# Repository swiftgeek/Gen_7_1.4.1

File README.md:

Known issues:

* PA6 missing trace to MCU and a short between PA6/PA7. Upstream `.pcb` file
doesn't match gerbers and PDFs/PNGs
* Board outline doesn't work well with OBV

TODO:

* Try importing gerber traces/layout into `pcb`/`pcbnew`, otherwise
set gerber render and background and try laying traces over it exactly.
* Generate PDFs and gerbers once fixed

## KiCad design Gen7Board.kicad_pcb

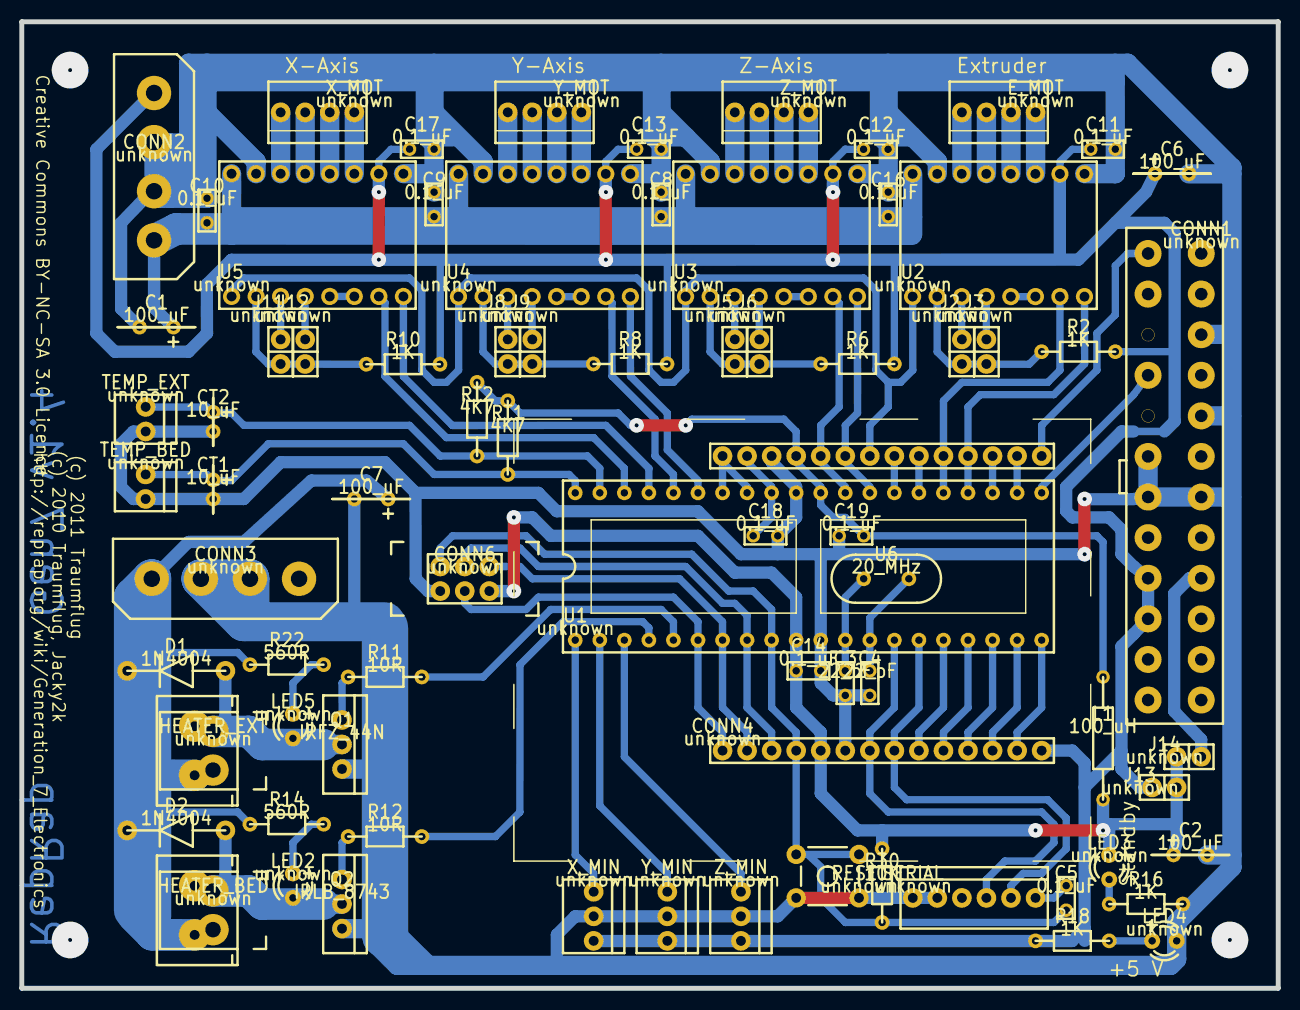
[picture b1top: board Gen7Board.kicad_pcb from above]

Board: 2 copper layers, 130.0 x 100.0 mm, 76 parts (0 on the bottom side), 84 nets.

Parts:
C1: 100_uF; RCY3mm5_dup15
C2: 100_uF; RCY3mm5_dup26
C3: 22_pF; ACY100_dup1
C4: 22_pF; ACY100_dup13
C5: 0.1_uF; ACY100_dup7
C6: 100_uF; RCY3mm5
C7: 100_uF; RCY3mm5_dup42
C8: 0.1_uF; ACY100_dup36
C9: 0.1_uF; ACY100_dup37
C10: 0.1_uF; ACY100_dup38
C11: 0.1_uF; ACY100_dup39
C12: 0.1_uF; ACY100
C13: 0.1_uF; ACY100_dup0
C14: 0.1_uF; ACY100_dup2
C16: 0.1_uF; ACY100_dup14
C17: 0.1_uF; ACY100_dup33
C18: 0.1_uF; ACY100_dup34
C19: 0.1_uF; ACY100_dup35
CONN1: unknown; ATX20+4-1
CONN2: unknown; MOLEX_4_PIN
CONN3: unknown; MOLEX_4_PIN_dup40
CONN4: unknown; ExtensionBoard
CONN6: unknown; ICSP_HEADER
CT1: 10_uF; RCY2mm_dup50
CT2: 10_uF; RCY2mm
D1: 1N4004; 1N4004_dup48
D2: 1N4004
E_MOT: unknown; 100-4-1_dup51
HEATER_BED: unknown; Combi-2-1_dup44
HEATER_EXT: unknown; Combi-2-1
J2: unknown; JUMPER2_1_dup22
J3: unknown; JUMPER2_1_dup23
J5: unknown; JUMPER2_1_dup24
J6: unknown; JUMPER2_1_dup25
J8: unknown; JUMPER2_1_dup3
J9: unknown; JUMPER2_1_dup6
J11: unknown; JUMPER2_1_dup4
J12: unknown; JUMPER2_1_dup5
J13: unknown; JUMPER2_1
J14: unknown; JUMPER2_1_dup9
L1: 100_uH; ACY500_1
LED2: unknown; LED3_1_dup45
LED3: unknown; LED3_1_dup8
LED4: unknown; LED3_1_dup12
LED5: unknown; LED3_1
Q1: IRFZ_44N; TO-220-1
Q2: IRLB_8743; TO-220-1_dup41
R2: 1K; ACY300_1_dup27
R6: 1K; ACY300_1_dup28
R8: 1K; ACY300_1_dup29
R10: 1K; ACY300_1_dup30
R11: 10R; ACY300_1_dup46
R12: 10R; ACY300_1_dup43
R14: 560R; ACY300_1_dup47
R16: 1K; ACY300_1_dup11
R18: 1K; ACY300_1_dup31
R22: 560R; ACY300_1
R30: 10K; ACY300_1_dup20
RESET: unknown; MJTP1230-1
RT1: 4K7; ACY300_1_dup32
RT2: 4K7; ACY300_1_dup10
SERIAL: unknown; 100-6-1
TEMP_BED: unknown; 100-2-1
TEMP_EXT: unknown; 100-2-1_dup49
U1: unknown; DIP40_1
U2: unknown; POLOLUSTEPPER-1_dup17
U3: unknown; POLOLUSTEPPER-1_dup19
U4: unknown; POLOLUSTEPPER-1
U5: unknown; POLOLUSTEPPER-1_dup18
U6: 20_MHz; CRYSTAL_AS
X_MIN: unknown; 100-3-1
X_MOT: unknown; 100-4-1
Y_MIN: unknown; 100-3-1_dup16
Y_MOT: unknown; 100-4-1_dup52
Z_MIN: unknown; 100-3-1_dup21
Z_MOT: unknown; 100-4-1_dup53

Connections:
+3.3V_ATX: CONN1.11, CONN4.15
+5V: C6.1, C11.2, C12.2, C13.2, C17.2, CONN1.19, CONN1.20, CONN2.4, CONN4.14, J13.1, R2.1, R6.1, R8.1, R10.1, R18.1, U2.10, U3.10, U4.10, U5.10, X_MIN.3, Y_MIN.3, Z_MIN.3
+5VSB: C2.1, C14.2, CONN4.5, CONN6.2, J13.2, J14.1, L1.1, LED3.1, R30.2, U1.10
+5VSB_ATX: CONN1.9, J14.2
+5VSB_AVCC: C19.1, CONN4.25, L1.2, RT1.2, RT2.2, U1.30
AREF: C18.1, CONN4.27, U1.32
E_1A: E_MOT.2, U2.12
E_1B: E_MOT.1, U2.11
E_2A: E_MOT.3, U2.13
E_2B: E_MOT.4, U2.14
E_5V_R: J2.2, J3.2, R2.2, U2.2
E_MS2: J2.1, U2.3
E_MS3: J3.1, U2.4
E_SLP_RST: U2.5, U2.6
GND: C1.2, C2.2, C3.2, C4.2, C6.2, C7.2, C8.2, C9.2, C10.2, C11.1, C12.1, C13.1, C14.1, C16.2, C17.1, C18.2, C19.2, CONN1.3, CONN1.5, CONN1.7, CONN1.16, CONN1.17, CONN2.2, CONN2.3, CONN3.2, CONN3.3, CONN4.6, CONN4.26, CONN6.6, CT1.2, CT2.2, LED4.2, Q1.3, Q2.3, R16.2, RESET.1, SERIAL.1, SERIAL.2, TEMP_BED.2, TEMP_EXT.2, U1.11, U1.31, U2.9, U2.15, U3.9, U3.15, U4.9, U4.15, U5.9, U5.15, X_MIN.2, Y_MIN.2, Z_MIN.2
GND_HEATER_BED: D2.2, HEATER_BED.2, LED2.2, Q2.2
GND_HEATER_EXT: D1.2, HEATER_EXT.2, LED5.2, Q1.2
LED2_R: LED2.1, R14.2
LED3_R: LED3.2, R16.1
LED4_R: LED4.1, R18.2
LED5_R: LED5.1, R22.2
PA0_TEMP_BED: CT1.1, RT1.1, TEMP_BED.1, U1.40
PA1_TEMP_EXT: CT2.1, RT2.1, TEMP_EXT.1, U1.39
PA2_X_STEP: U1.38, U5.7
PA3_X_DIR: U1.37, U5.8
PA4_Y_STEP: U1.36, U4.7
PA5_Y_DIR: U1.35, U4.8
PA6_MOT_EN: CONN4.22, CONN4.28, U1.33, U1.34, U2.1, U3.1, U4.1, U5.1
PB0_X_MIN: U1.1, X_MIN.1
PB1_Y_MIN: U1.2, Y_MIN.1
PB2_Z_MIN: U1.3, Z_MIN.1
PB3_HEATER_BED: R12.2, U1.4
PB3_HEATER_BED_R: Q2.1, R12.1
PB3_HEATER_EXT_R: Q1.1, R11.1
PB4_HEATER_EXT: R11.2, U1.5
PB5_ICSP_MOSI: CONN4.1, CONN6.4, U1.6
PB6_ICSP_MISO: CONN4.2, CONN6.1, U1.7
PB7_ICSP_SCK: CONN4.3, CONN6.3, U1.8
PC0_SCL: CONN4.16, U1.22
PC1_SDA: CONN4.17, U1.23
PC2_E_STEP: CONN4.18, U1.24, U2.8
PC3_E_DIR: CONN4.19, U1.25, U2.7
PC4_TDO: CONN4.20, U1.26
PC5_TDI: CONN4.21, U1.27
PC6_Z_DIR: CONN4.23, U1.28, U3.8
PC7_Z_STEP: CONN4.24, U1.29, U3.7
PD0_RXD0: CONN4.7, SERIAL.4, U1.14
PD1_TXD0: CONN4.8, SERIAL.5, U1.15
PD2_RXD1_INT0: CONN4.9, U1.16
PD3_TXD1_INT1: CONN4.10, U1.17
PD4_XCK1_OC1B: CONN4.11, U1.18
PD5_OC1A: CONN4.12, U1.19
PD6_OC2B_ICP: CONN4.13, U1.20
PD7_ATX_PS_ON: CONN1.14, U1.21
RESET: C5.1, CONN4.4, CONN6.5, R30.1, RESET.2, U1.9
RESET_C: C5.2, SERIAL.6
Vheat: C7.1, CONN3.1, D1.1, D2.1, HEATER_BED.1, HEATER_EXT.1, R14.1, R22.1
Vmot: C1.1, C8.1, C9.1, C10.1, C16.1, CONN2.1, U2.16, U3.16, U4.16, U5.16
XTAL1: C4.1, U1.13, U6.1
XTAL2: C3.1, U1.12, U6.2
X_1A: U5.12, X_MOT.2
X_1B: U5.11, X_MOT.1
X_2A: U5.13, X_MOT.3
X_2B: U5.14, X_MOT.4
X_5V_R: J11.2, J12.2, R10.2, U5.2
X_MS2: J11.1, U5.3
X_MS3: J12.1, U5.4
X_SLP_RST: U5.5, U5.6
Y_1A: U4.12, Y_MOT.2
Y_1B: U4.11, Y_MOT.1
Y_2A: U4.13, Y_MOT.3
Y_2B: U4.14, Y_MOT.4
Y_5V_R: J8.2, J9.2, R8.2, U4.2
Y_MS2: J8.1, U4.3
Y_MS3: J9.1, U4.4
Y_SLP_RST: U4.5, U4.6
Z_1A: U3.12, Z_MOT.2
Z_1B: U3.11, Z_MOT.1
Z_2A: U3.13, Z_MOT.3
Z_2B: U3.14, Z_MOT.4
Z_5V_R: J5.2, J6.2, R6.2, U3.2
Z_MS2: J5.1, U3.3
Z_MS3: J6.1, U3.4
Z_SLP_RST: U3.5, U3.6

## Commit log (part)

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2010-10-15 Add schematic symbol and data sheet for an H21LOB.
2010-10-17 Gen7Board.pcb: fix the layer grouping to actually have a working solder and component side.
2010-10-17 Fix the Molex KK 100 3-pin connector footprint to comply with the data sheet.
2010-10-18 Complete the Opto Endstop with the remaining footprints and create a PCB.
2010-10-30 Gen7Board: modify the schematic to match the recent turn of the endstop connectors in the PCB.
2010-10-30 Modified the ATmega symbol to show secondary pin symbols as well.
2010-10-30 Following a contribution by Lanthan: Made a footprint for the ICSP header with matching pin numbering and wired the thing into the pcb.
2010-12-09 Changed Opto Endstop connectors to match the layout of RAMPS.
    Yes, this is yet again and no, the endstops them selfs are not done yet.
2010-12-13 Board: moved the Reset button ...
    ... to gain space for moving the serial connector.
2010-12-15 Board, by Jacky2k: Allow traces between between reset switch pins.
    Also add a data sheet for that switch and rename the footprint accordingly.
2010-12-15 Board, by Jacky2k: move temperature sensors from port PB to PA.
    This is neccessary, as only port PA features analog inputs.
2010-12-15 Board: drop fuse R15 as well.
    Unfortunately, no simplification in the PCB layout this time.
2010-12-16 Board: remove one of the traces to the 5V pins of the ATX20 for simplification.
2010-12-16 Board: connected SLEEP and RESET directly.
    This is hinted in the breakout board data sheet on page 2 and
    page 4 of that document shows this pulls both pins high, due
    to an resistor already on that breakout board.
2010-12-17 Board: removed R1, R5, R7 and R9 as they appear to be obsolete.
    The obsoleteness was found by comparing with other circuits like
    RAMPS, Repic.
2010-12-17 Board: simplified and widened the traces under the Pololus.
    This was possible due to the last two changes.
2010-12-18 Revert "Board: raised R2, R6, R8 and R10 to 100K from 2K7."
    This was a silly idea, as there are internal pulldown-resistors.
    Changed them now to 1K to have more resistors of the same value.
2010-12-18 Board: corrected D1, D2 and D3's footprint.
    This included using a reverted symbol in the schematics, as
    schematics and layout didn't agree in pin numbering. Yes,
    even with only 2 pins something like this can be wrong.
2010-12-18 Removed this obsolete "work" file.
2010-12-18 Board: replaced the ATX12V connector with a Molex 4 pin one.
    More important here is to get the connector to the left side.
2010-12-19 Board: back into the 25 mil grid.
    An unfortunate feature of gEDA is, if you switch measurement units
    from mil to mm, the grid size changes also. This accidently happened
    when th big move was done a few commits earlier.
2010-12-19 Smaller C3, C4 footprints Changed the footprints of C3, C4 (capacitors for the crystal) to 100mil footprint for ceramic capacitors.
2010-12-19 Board: Changed footprint of more capacitors to 100mil.
2010-12-19 Increase the silk line thickness of the ATX20 to 10 mil.
    This is to match the DRC's expectations.
2010-12-19 Board: Connected heater/fan headers to the outside pins
2010-12-19 Board: Filter for AVCC A L/C Filter for AVCC was added and the 5V to 5VSB bridge jumper was moved
2010-12-19 Board: Moved wrong places GND line away from Q1
2010-12-20 Board: moved the ATmega a few mm up.
    This reliefs the space situation below the processor. Spotted
    by Jacky2k.
2010-12-20 Board: moved the Reset button a bit to the left.
    This makes room for the ICMP connector. Spotted by Jacky2k.
2010-12-21 Board: more space around the drill holes of FET Q1.
2010-12-21 Board: reviewed the TIP120 with it's TO-220 housing.
2011-01-08 Board: make C1, C2 and C6 all 100 uF.
2011-01-08 Board: give C5 a value, 0.1 uF.
2011-01-08 Board: raised copper around 3-pin Molex KK 100 header pins as well.
    The new copper size is 80 mil. Also previously drill sizes mismatched
    between the layout and the footprint.
2011-01-08 Board: removed H1 and H2 from the schematics.
    These two headers were disconneted a long time ago anyways,
    just cluttering up the schematics.
2011-01-08 Deleted unused footprint Molex KK 156-2.
2011-01-11 Board, by Jacky2k: Added 10K pull-ups for I2C.
2011-01-11 Board: mark all non-GND tracks as "clearline".
    This doesn't change the appearance of the board, but makes laying
    a ground plane much easier.
2011-01-12 Board: align mounting holes, and make them pure drill holes.
2011-01-24 Board: Made the board a little bit smaller.
    Moved the mounting holes accordingly. The board is now 100 x 130 mm.
2011-01-24 Board: review the ICMP header, needs more space.
    Also added a data sheet and fit the reviewed footprint into the
    layout.
2011-01-24 Board, by Jacky2k: more copper around the jumper headers.
    This includes the 5-pin MISC header.
    Note there's a bug in the very popular 2009 version of PCB,
    which disallows the usage of dashs (-) in some footprint file names.
2011-01-24 Board: switch remaining 100 nF value to 0.1 uF to match majority.
    No functional change.
2011-01-25 Board: drill size of the Molex 156 connectors is now 70 mil (1.78 mm).
2011-01-27 Board: add the connection to all EN pins in the schematic as well.
    Accidently, this was forgotten when drawing this into the board's
    layout, so the board remains unchanged.
2011-02-02 Board: move motor connectors up 25 mil to make room for the connector's snappers.
2011-02-02 Board: reviewed all polarized capacitors.
    This included a new footprint for the 10uF ones. Footprint
    for the 100uF ones are unchanged, as 35V versions have the currently
    designed spacing. 25V ones are smaller, but the Pololus are spec'd
    for 35V, so some people may choose to use that current.
2011-02-02 Board: tidied up texts a bit.
    No functional, track or element change.
2011-02-26 Gen7Board: change a "4k7" to "4K7".
    Component values have to match case-sensitive to be recognized
    as being the same.
2011-03-07 Both Endstops: reduce drill size for the 3 mm LEDs to 30 mil / 0.76 mm.
    This also reduces the number of drills from 4 to 3, which is about as
    good as we can get it.
2011-03-07 Endstops: make LEDs have round pins.
2011-03-07 Endstops: re-apply a small copper ring around mounting holes.
    This should avoid Visolate to pull an isolation path right through
    these mounting holes, risking a short by the mounting screw.
2011-03-07 Board: raise the reset switch drill holes to 40 mil = 1.02 mm.
2011-03-07 Board: use the footprints also used in the Endstops.
    This also raises the resistor's drill sizes to 30 mil, getting
    the 28 mil drill closer to be obsolete.
2011-03-07 Board: drill the ATmega's socket with 30 mil as well.
2011-03-07 Board: replace the 5 mm LEDs with 3 mm ones.
    This also removes the requirement for the 43 mil drill, so we have
    now 9 drill sizes.
2011-03-07 Board: use the same mounting holes as with the Endstops.
    This also gives them a small copper ring, avoiding shorts by the
    mounting screw when milling with Voronoi paths.
2011-03-08 Board: hide the enforced names of the motor connectors.
    There was descriptive text already, which was slightly moved
    away from the outline.
2011-03-09 Board: made diode pins round and only 40 mil = 1.02 mm drill size.
2011-03-09 Board: reduced drill size of the serial connector to 40 mil.
    Also fixed the solder mask of this connector.
2011-03-10 Board: make 10 uF caps have all round pins and a plus sign.
2011-03-10 Board: fix the MISC header's solder mask.
2011-03-10 Board: make 100 uF caps have all round pins and a plus sign.
2011-03-10 Board: add a solder mask relief to all vias.
    We have a unusual requirement here, as vias are not really
    used as vias, mut as pin holes for wire bridges.
2011-03-10 Board, Endstops: add a plus sign to the LEDs silk screen.
2011-03-10 Remove an unused footprint.
2011-03-10 Board: fix solder mask of 2-pin jumpers.
2011-03-10 Board: connect HEATER1 and HEATER2 with PWM-able pins.
    Sometimes it's astonishing how long it takes to find such essential
    flaws.
2011-03-14 Board: make all tracks meant as wire bridges 50 mil wide.
    Previously, they had different widths.
2011-03-28 Make Release 1.1.
2011-04-06 Added symbol and footprint for the TCST optical sensor.
    The footprint is for the TCST 11xx series, which doesn't have
    mounting holes.
2011-05-10 Board: changed the version print from 1.1 to 1.2.
2011-05-11 Endstop: add plus signs to the photo interrupter footprint.
    This should clarify how to insert that thing into the PCB.
2011-05-23 Add combined footprint for the motor headers.
    As ever only one of Molex 156 of AKL 220 connector can be soldered
    in, having two seperate symbols in the schematic isn't ideal. So,
    the goal is now to do this redundacy in the footprint only.
2011-05-25 Removed the Molex .156 and the AKL 220 connector.
    They're no longer used and were replaced by the Combi-4 footprint.
2011-05-25 Remove the MOSFET for the fan.
    This has three reasons:
    1 A questionaire resulted in nobody actually using a fan.
    2 If you really want a fan, connect it to the power supply
    directly. Like the PSU, it will switch off at end of printing.
    3 Cost and board space, of course. Cost saving is about EUR 1.-.
    No worries, the board space will be reused quickly, bigger headers
2011-05-25 Replace the heater connectors with that new Combi-2 type.
    Several enhancements:
    - Only two pins -> less confusion.
    - Thicker pins -> more current possible.
    - You can use screw terminals.
2011-05-26 Add a Molex KK100 2-pin header.
2011-06-03 Removed the three-jumper, as the plans for this have vanished.
2011-06-03 Board: replaced the footprint for the ATX20 connector.
    The footprint has now 24 pins for compatibility with
    ATX24 power supplies.
2011-06-06 Board: the debug LED is back!
2011-06-06 Board: add another disk power type connector for supplying heaters.
    Also, the 12 volts stuff was divided into two parts. This allows
    to have different voltages for heaters and motors without making
    things more complex for newbie users.
2011-06-07 Board: made the 20 MHz crystal the default.
2011-06-07 Board: reduced the drill size of the MOSFETs to 40 mil = 1.02 mm.
    In the data sheet 0.66 to 0.93 mm are specified, so this is safe.
    Seven drill sizes are left, now.
2011-06-08 Board: reduced the ATX24's drill size to 1.3 mm.
    This was 1.4 mm and takes account for the fact Gen7 is single sided,
    so no solder can flow into the hole anyways.
2011-06-08 Board: made traces from the MOSFETs a bit shorter and thicker.
    There's a lot of current and this also makes a bit more room.
2011-06-08 Both PCBs: raise minimum track width to 30 mil.
    Was 20 mil before. According to users of the toner etching method,
    wider tracks are more reliable. So, increasing track width without
    lowering minimum copper track (important for isolation milling)
    is a good thing.
2011-06-11 Board: make the MOSFETs upright.
    This should allow better cooling and attaching a heatsink. Effectively,
    it just replaces the silk of the footprint ...
    Also made the GND trace there even thicker.
2011-06-14 Board: bump printed version number to 1.3, note new licence.
2011-06-15 Board: align CONN3 to CONN2.
    Also purely cosmetic.
2011-06-15 Board: aligned Temp connectors with the surrounding connectors.
    Another cosmetics without functional change.
2011-06-29 Board: fix a misaligned mounting hole.
    The misalignment was probably introduced unintentionally.
2011-07-21 Make Release 1.3.
2012-12-09 Make Gen7Board 1.4 release.
    New Features:
    - Added the extension header.
    - Moved motor heaters from KK156 to KK100 ones.
    - Reduced the number of endstops to 3.
    - Connect the thermistor to 5V Standby.
    - Better GND routing for even more accurate temperature readings.
2023-02-22 Add missing symbols from Gen7Board-AVR-1.5
2023-02-22 Initial commit with PCB/SCH changes
2023-02-22 Final changes for public buggy 1.4.1 PCB

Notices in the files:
Gen7Board.kicad_pcb:
(c) 2010 Traumflug, Jacky2k
(c) 2011 Traumflug
Creative Commons BY-NC-SA 3.0 Licence
